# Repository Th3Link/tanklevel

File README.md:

# TL-136 Liquid Level Sensor

This project provides a solution for **measuring the liquid level in tanks**, such as rainwater tanks, using the **TL-136 pressure sensor**. It is designed for **easy integration with home automation systems**, connecting via **Wi-Fi** or **Ethernet**.

## Features

- Measures liquid levels in tanks accurately using the TL-136 sensor.  
- Connectivity: Wi-Fi or Ethernet for integration with smart home systems.  
- Compact design to fit in a **3-way IP68 junction box** (minimum inner dimensions: 90 × 110 mm).  
- PCB target size: 80 × 60 mm.  
- Powered by a **24V supply**, e.g., MEAN WELL APV-8-24 (8W).  

## Inspiration

This project is **heavily inspired** by:  
[Nachbelichtet – Measuring Water Levels in Cisterns with Home Assistant, ESPHome, and TL-136](https://nachbelichtet.com/wasserstand-in-zisternen-mit-homeassistant-esphome-und-tl-136-drucksensor-messen)

## License

This project is licensed under the **CERN Open Hardware License – Strongly Reciprocal (CERN OHL-S)**.  
See [`LICENSE.txt`](LICENSE.txt) for details.

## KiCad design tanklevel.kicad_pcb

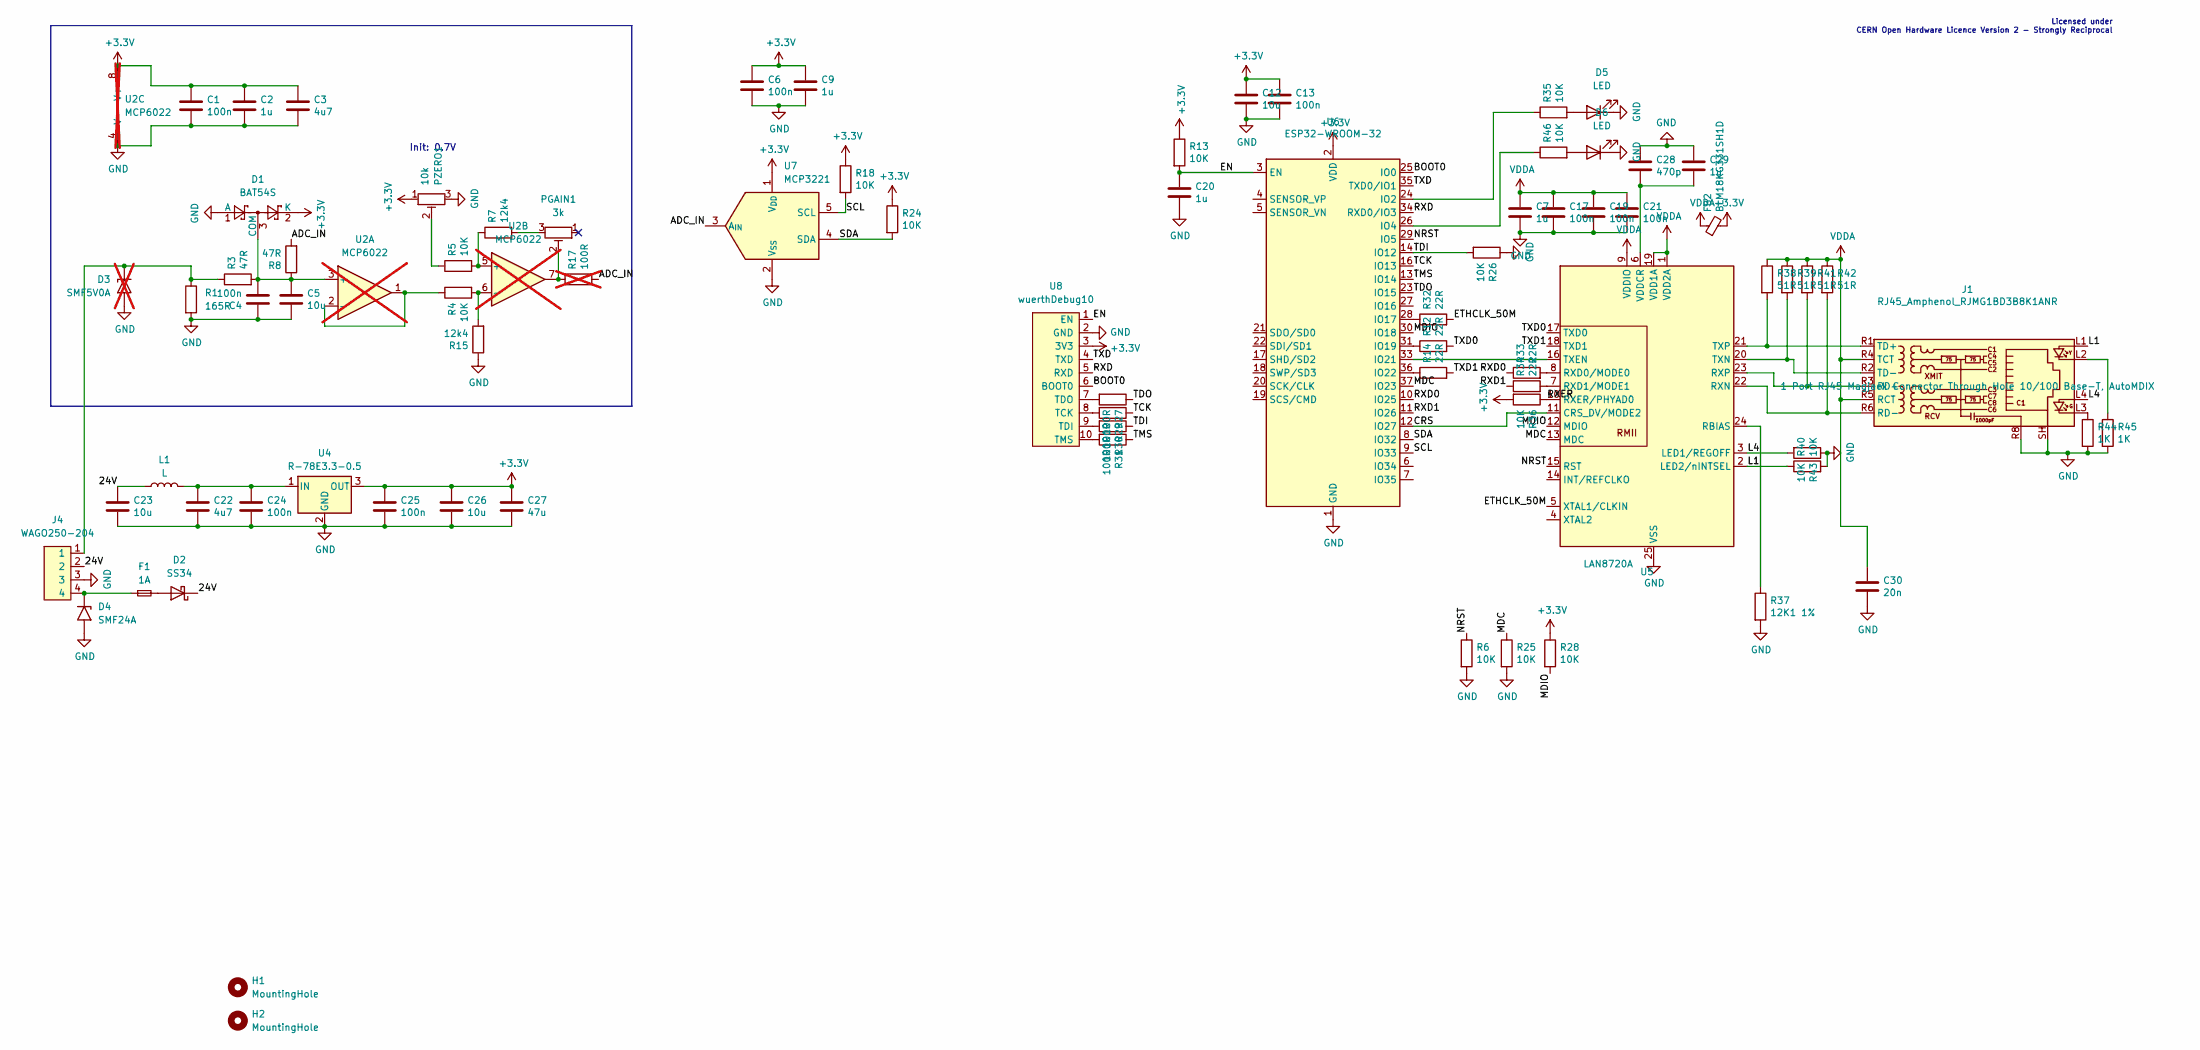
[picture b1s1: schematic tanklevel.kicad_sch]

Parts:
C1, C4, C6, C13, C17, C19, C21, C24, C25: 100n; C_0603_1608Metric; LCSC PN C14663
C2, C7, C9, C20, C29: 1u; C_0805_2012Metric; LCSC PN C28323
C3: 4u7; C_0805_2012Metric; LCSC PN C1779
C5, C12, C26: 10u; C_0805_2012Metric; LCSC PN C15850
C22: 4u7; C_1206_3216Metric; LCSC PN C51205
C23: 10u; C_1206_3216Metric; LCSC PN C13585
C27: 47u; C_1210_3225Metric; LCSC PN C77101
C28: 470p; C_0603_1608Metric; LCSC PN C85979
C30: 20n; C_0603_1608Metric; LCSC PN C282065
D1: BAT54S; SOT-23; LCSC PN C7420333
D2: SS34; D_SMA; LCSC PN C8678
D3: SMF5V0A; D_SMF; LCSC PN C19077497; not fitted
D4: SMF24A; D_SMF; LCSC PN C19077514
D5, D6: LED; LED_0603_1608Metric; LCSC PN C157741
F1: 1A; Fuse_0603_1608Metric; LCSC PN C151139
FB2: BLM18KG331SH1D; L_0603_1608Metric; LCSC PN C710376
H1, H2: MountingHole; MountingHole_2.2mm_M2_DIN965
J1: RJ45_Amphenol_RJMG1BD3B8K1ANR
J4: WAGO250-204
L1: L; RLS-126-R
PGAIN1: 3k; Potentiometer_Bourns_3296W_Vertical
PZERO1: 10k; Potentiometer_Bourns_3296W_Vertical
R1: 165R; R_1206_3216Metric; LCSC PN C870446
R3, R8: 47R; R_0603_1608Metric; LCSC PN C114623
R4, R5, R6, R13, R18, R24, R25, R26, R28, R35, R36, R40, R43, R46: 10K; R_0603_1608Metric; LCSC PN C140867
R7, R15: 12k4; R_0603_1608Metric; LCSC PN C137798
R12, R14, R32, R33, R34: 22R; R_0603_1608Metric; LCSC PN C138283
R17: 100R; R_0603_1608Metric; LCSC PN C122970; not fitted
R27, R29, R30, R31: 100R; R_0603_1608Metric; LCSC PN C122970
R37: 12K1 1%; R_0603_1608Metric; LCSC PN C245906
R38, R39, R41, R42: 51R; R_0603_1608Metric; LCSC PN C23197
R44, R45: 1K; R_0603_1608Metric; LCSC PN C22548
U2: MCP6022; SOIC-8_3.9x4.9mm_P1.27mm; LCSC PN C57639; not fitted
U4: R-78E3.3-0.5; Converter_DCDC_RECOM_R-78E-0.5_THT
U5: LAN8720A; QFN-24-1EP_4x4mm_P0.5mm_EP2.6x2.6mm; LCSC PN C45223
U6: ESP32-WROOM-32; LCSC PN C701341
U7: MCP3221; SOT-23-5; LCSC PN C36310
U8: wuerthDebug10; wuerth10

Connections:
+3.3V: C1.1, C2.1, C3.1, C6.1, C9.1, C12.1, C13.1, C25.1, C26.1, C27.1, D1.2 (K), FB2.2, PZERO1.1, R13.1, R18.1, R24.1, R28.1, R36.2, U2.8 (V+), U4.3 (OUT), U6.2 (VDD), U7.1 (V_{DD}), U8.3 (3V3)
/24V: C23.1, D2.1 (K), J4.2, L1.1
/ADC_IN: R8.2, R17.2, U7.3 (A_{IN})
/BOOT0: U6.25 (IO0), U8.6 (BOOT0)
/CRS: U5.11 (CRS_DV/MODE2), U6.12 (IO27)
/EN: C20.1, R13.2, U6.3 (EN), U8.1 (EN)
/ETHCLK_50M: R32.2, U5.5 (XTAL1/CLKIN)
/L1: J1.L1, R40.1, U5.2 (LED2/nINTSEL)
/L4: J1.L4, R43.2, U5.3 (LED1/REGOFF)
/MDC: R25.1, U5.13 (MDC), U6.37 (IO23)
/MDIO: R28.2, U5.12 (MDIO), U6.30 (IO18)
/NRST: R6.1, U5.15 (RST), U6.29 (IO5)
/RXD: U6.34 (RXD0/IO3), U8.5 (RXD)
/RXD0: R33.1, U6.10 (IO25)
/RXD1: R34.1, U6.11 (IO26)
/RXER: R36.1, U5.10 (RXER/PHYAD0)
/SCL: R18.2, U6.9 (IO33), U7.5 (SCL)
/SDA: R24.2, U6.8 (IO32), U7.4 (SDA)
/TCK: R29.1, U6.16 (IO13)
/TDI: R26.2, R30.1, U6.14 (IO12)
/TDO: R27.1, U6.23 (IO15)
/TMS: R31.1, U6.13 (IO14)
/TXD: U6.35 (TXD0/IO1), U8.4 (TXD)
/TXD0: R12.2, U5.17 (TXD0)
/TXD1: R14.2, U5.18 (TXD1)
GND: C1.2, C2.2, C3.2, C4.1, C5.2, C6.2, C7.2, C9.2, C12.2, C13.2, C17.2, C19.2, C20.2, C21.2, C22.2, C23.2, C24.2, C25.2, C26.2, C27.2, C28.1, C29.1, C30.2, D1.1 (A), D3.2 (A2), D4.2 (A2), D5.1 (K), D6.1 (K), J1.R8, J1.SH, J4.3, PZERO1.3, R1.2, R6.2, R15.1, R25.2, R26.1, R37.2, R40.2, R43.1, R44.2, R45.2, U2.4 (V-), U4.2 (GND), U5.25 (VSS), U6.1 (GND), U6.15 (GND), U6.38 (GND), U6.39 (GND), U7.2 (V_{SS}), U8.2 (GND)
unnamed: C4.2, C5.1, D1.3 (COM), R3.2, R8.1, U2.3 (+)
unnamed: D2.2 (A), F1.2
unnamed: D3.1 (A1), J4.1, R1.1, R3.1
unnamed: D4.1 (A1), F1.1, J4.4
unnamed: D5.2 (A), R35.2
unnamed: D6.2 (A), R46.2
unnamed: J1.L2, R45.1
unnamed: J1.L3, R44.1
unnamed: J1.R3 (RD+), R41.2, U5.23 (RXP)
unnamed: J1.R6 (RD-), R42.2, U5.22 (RXN)
unnamed: J1.R1 (TD+), R38.2, U5.21 (TXP)
unnamed: J1.R2 (TD-), R39.2, U5.20 (TXN)
unnamed: PGAIN1.2, R17.1, U2.7
unnamed: PGAIN1.3, R7.2
unnamed: PZERO1.2, R5.1
unnamed: R4.1, U2.1, U2.2 (-)
unnamed: R5.2, R7.1, U2.5 (+)
unnamed: R4.2, R15.2, U2.6 (-)
unnamed: C22.1, C24.1, L1.2, U4.1 (IN)
unnamed: R37.1, U5.24 (RBIAS)
unnamed: R33.2, U5.8 (RXD0/MODE0)
unnamed: R34.2, U5.7 (RXD1/MODE1)
unnamed: U5.16 (TXEN), U6.33 (IO21)
unnamed: C28.2, C29.2, U5.6 (VDDCR)
unnamed: R35.1, U6.24 (IO2)
unnamed: R46.1, U6.26 (IO4)
unnamed: R32.1, U6.28 (IO17)
unnamed: R12.1, U6.31 (IO19)
unnamed: R14.1, U6.36 (IO22)
unnamed: R29.2, U8.8 (TCK)
unnamed: R30.2, U8.9 (TDI)
unnamed: R27.2, U8.7 (TDO)
unnamed: R31.2, U8.10 (TMS)
VDDA: C7.1, C17.1, C19.1, C21.1, C30.1, FB2.1, J1.R4 (TCT), J1.R5 (RCT), R38.1, R39.1, R41.1, R42.1, U5.1 (VDD2A), U5.9 (VDDIO), U5.19 (VDD1A)

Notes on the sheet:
Licensed under CERN Open Hardware Licence Version 2 - Strongly Reciprocal
Init: 0.7V

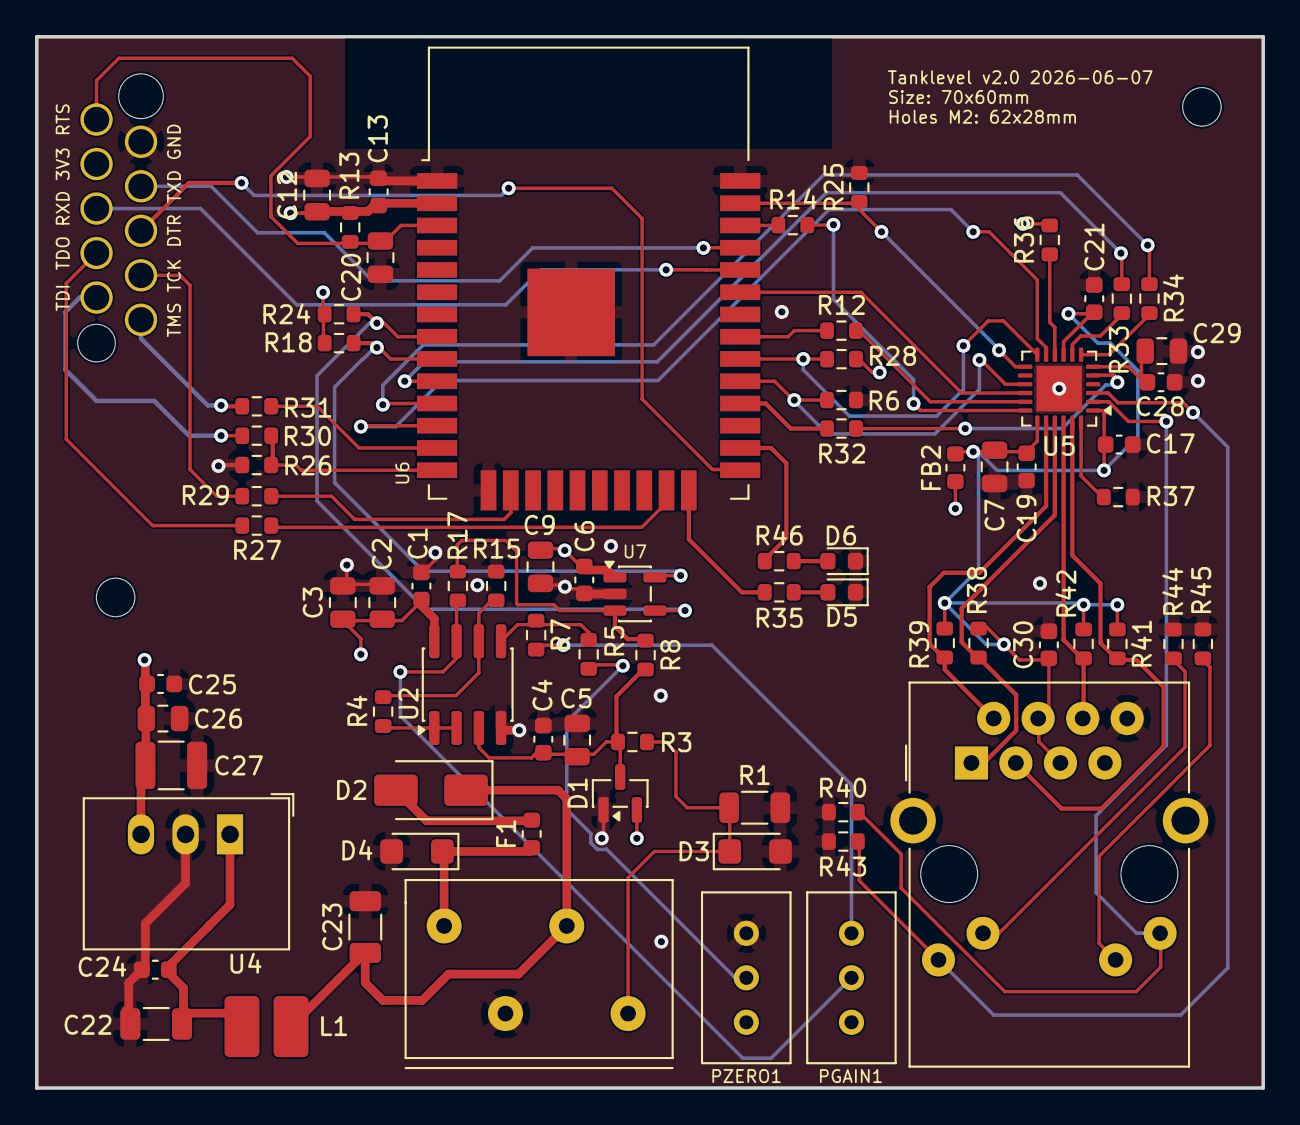
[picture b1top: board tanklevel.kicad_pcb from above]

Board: 4 copper layers, 70.0 x 60.0 mm, 80 parts (0 on the bottom side), 60 nets.

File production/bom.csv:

Designator,Footprint,Quantity,Value,LCSC Part #
"C1, C13, C17, C19, C21, C24, C25, C4, C6",0603,9,100n,C14663
"C12, C26, C5",0805,3,10u,C15850
"C2, C20, C29, C7, C9",0805,5,1u,C28323
C22,1206,1,4u7,C51205
C23,1206,1,10u,C13585
C27,1210,1,47u,C77101
C28,0603,1,470p,C85979
C3,0805,1,4u7,C1779
C30,0603,1,20n,C282065
D1,SOT-23,1,BAT54S,C7420333
D2,D_SMA,1,SS34,C8678
D4,D_SMF,1,SMF24A,C19077514
"D5, D6",0603,2,LED,C157741
F1,0603,1,1A,C151139
FB2,0603,1,BLM18KG331SH1D,C710376
R1,1206,1,165R,C870446
"R12, R14, R32, R33, R34",0603,5,22R,C138283
"R13, R18, R24, R25, R26, R28, R35, R36, R4, R40, R43, R46, R5, R6",0603,14,10K,C140867
"R15, R7",0603,2,12k4,C137798
"R27, R29, R30, R31",0603,4,100R,C122970
"R3, R8",0603,2,47R,C114623
R37,0603,1,12K1 1%,C245906
"R38, R39, R41, R42",0603,4,51R,C23197
"R44, R45",0603,2,1K,C22548
U5,QFN-24-1EP_4x4mm_P0.5mm_EP2.6x2.6mm,1,LAN8720A,C45223
U6,ESP32-WROOM-32,1,ESP32-WROOM-32,C701341
U7,SOT-23-5,1,MCP3221,C36310

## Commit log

2025-09-16 feat: Initial commit
2026-03-14 feat: Switch back to LAN8720A
2026-06-07 feat: Update to tanklevel v2 pcb
2026-06-07 feat: Create fab output
